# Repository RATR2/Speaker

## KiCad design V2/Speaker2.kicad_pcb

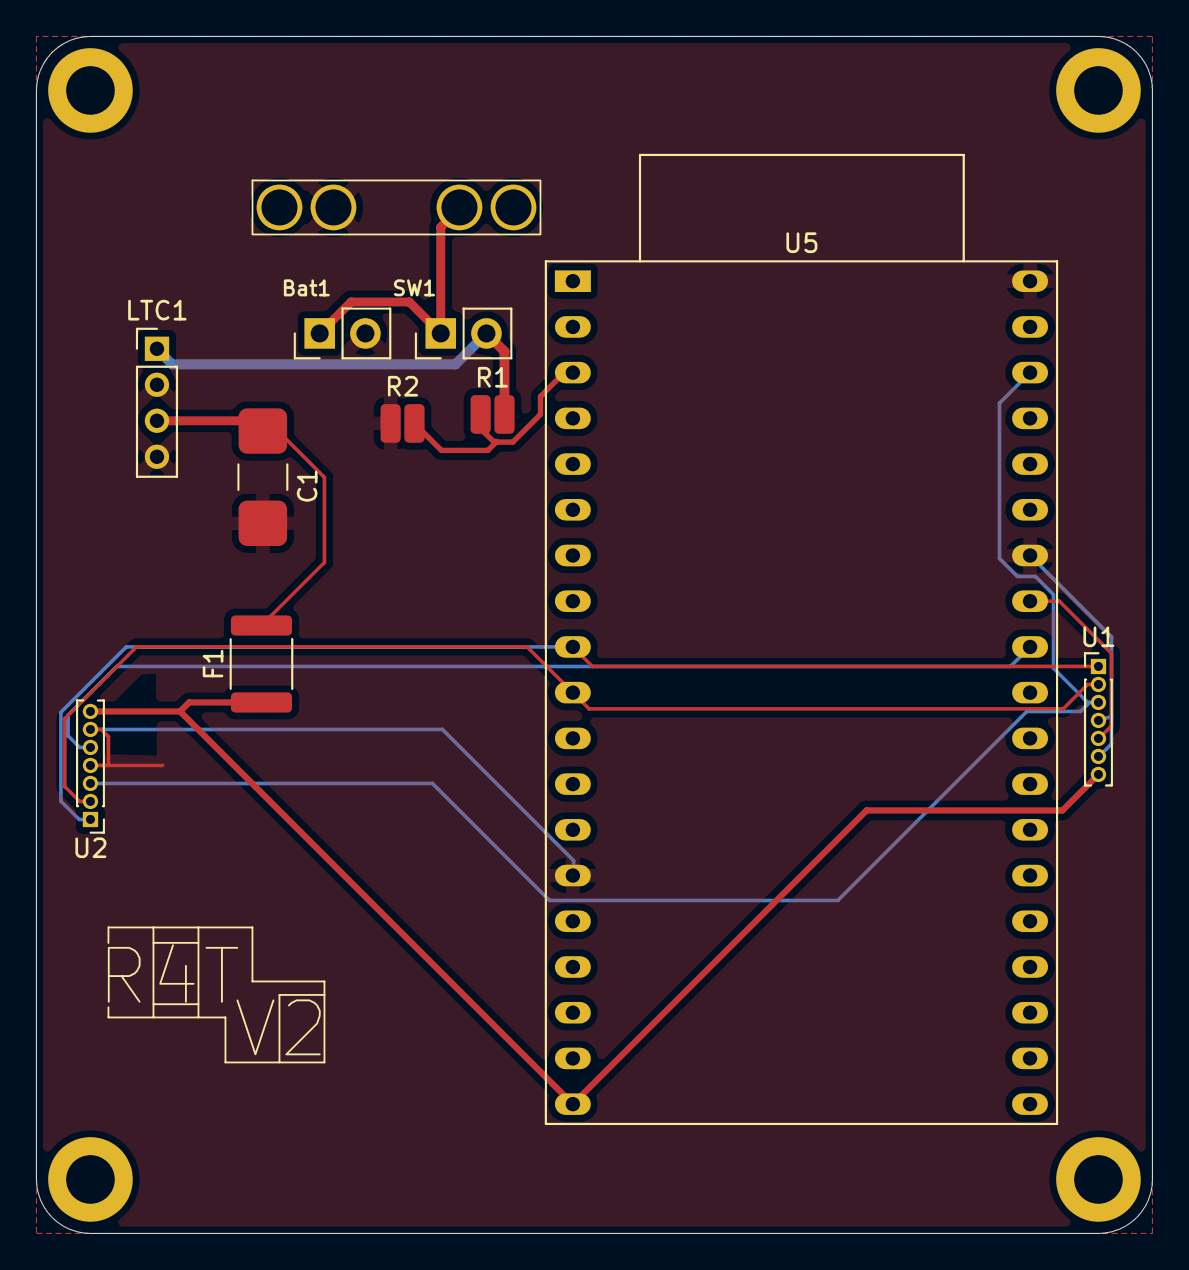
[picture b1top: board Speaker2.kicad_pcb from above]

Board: 2 copper layers, 62.0 x 66.5 mm, 15 parts (0 on the bottom side), 11 nets.

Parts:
Bat1: Conn_01x02; PinHeader_1x02_P2.54mm_Vertical
C1: C_US; C_1000uF_PadMount_P5.0mm
F1: Polyfuse; Fuse_1812_4532Metric
LTC1: PinHeader_1x04_P2.00mm_Vertical
R1, R2: r=10k; R_0508_1220Metric_Pad1.12x2.15mm_HandSolder
SS1, SS4: MountingHole_2.7mm_M2.5_DIN965_Pad
SS2, SS3: MountingHole_2.7mm; MountingHole_2.7mm_M2.5_DIN965_Pad
SW1: SW_SPST; PinHeader_1x02_P2.54mm_Vertical
U1, U2: MAX98357A; PinHeader_1x07_P1.00mm_Vertical
U3: Bat_Charger
U5: ESP32-DevKitC

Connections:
unnamed: Bat1.1, SW1.1 (A), U3.3 (BAT+)
unnamed: Bat1.2, C1.2, LTC1.2 (IN-), LTC1.4 (OUT-), R2.1, U1.4 (GAIN_SLOT), U1.6 (GND), U2.4 (GAIN_SLOT), U2.6 (GND), U3.2 (BAT-), U5.14 (GND), U5.32 (GND), U5.38 (GND)
unnamed: LTC1.1 (IN+), R1.2, SW1.2 (B)
unnamed: C1.1, F1.2, LTC1.3 (OUT+)
unnamed: U1.2 (BCLK), U2.2 (BCLK), U5.10 (DAC_2/ADC2_CH9/GPIO26)
unnamed: U1.3 (DIN), U2.3 (DIN), U5.36 (GPIO22)
unnamed: U1.1 (LRCLK), U2.1 (LRCLK), U5.9 (DAC_1/ADC2_CH8/GPIO25)
unnamed: U1.5 (~SD_MODE), U5.31 (GPIO19)
unnamed: U2.5 (~SD_MODE), U5.30 (GPIO18)
unnamed: F1.1, U1.7 (VDD), U2.7 (VDD), U5.19 (5V)
unnamed: R1.1, R2.2, U5.3 (SENSOR_VP/GPIO36/ADC1_CH0)

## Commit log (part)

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2025-10-21 Speaker3
2025-10-22 slight change
2025-11-13 speakerupd
